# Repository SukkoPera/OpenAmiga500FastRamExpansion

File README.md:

# OpenAmiga500FastRamExpansion
OpenAmiga500FastRamExpansion is an Open Hardware 4/8 MB Fast RAM Expansion for the Commodore Amiga 500 Computer.

### Summary
Most low-end Amiga models only came with *Chip RAM*. "Big Box" models allowed for a different type of memory to be installed, known as *Fast RAM*, where *fast* means that it's dedicated to the main processor, so that it doesn't have to compete with the other chips in order to gain access to it (as is the case with Chip RAM). While both Chip and Fast RAM are limited in size, you can have at least a few MB of the latter on all Amigas (usually up to 8), while the former can never exceed 2 MB.

OpenAmiga500FastRamExpansion will allow you to add 4 or 8 MB of Fast RAM to your Amiga 500. This way you will be able to run more applications at once and more quickly. If you combine it with [a chip RAM expansion](http://eab.abime.net/showthread.php?t=85395), you will also be able to run almost all games supported by WHDLoad, pushing your Amiga to its limits.

OpenAmiga500FastRamExpansion is basically a clone of [a RAM expansion produced by Kipper2K a few years ago](http://eab.abime.net/showthread.php?t=64218), based on [an earlier design by lvd/NedoPC](http://lvd.nedopc.com/Projects/a600_8mb/index.html). He has since stopped producing and selling these cards and I thought it was a pity that he didn't open his designs and actually took all of them down, as this card is quite cheap to build and really useful. So I set about recreating it from scratch.

### Memory Compatibility
The required RAM Type is 16 Mbit (1M×16) DRAM in the SOJ-42 package with up to 70-80 ns access time. It is 5v-only DRAM (not SD(!)RAM) often found in old 72-pin SIMMs, EDO chips might work or not. All chips having *8160* in their part number should be OK.

|Model          |Maker             |Tested             |Working            |Data Sheet                                                                                                                                                                 |Notes                                                                                |
|---------------|------------------|:-----------------:|:-----------------:|:-------------------------------------------------------------------------------------------------------------------------------------------------------------------------:|-------------------------------------------------------------------------------------|
|AS4C1M116E5    |Alliance          |||                                                                                                                                                                           |Tested by @Homer799                                                                  |
|GM71C18160     |Hynix/LGS         |||                                                                    |Tested by lvd in his original project                                                |
|HY5118164B     |Hynix             |||                                                                                                                                                                           |Tested by @Sgw32                                                                     |
|KM416C1200AJ   |SEC               |||                                                                                                                                                                           |Reported working by Ronald Baer                                                      |
|KM416C1204AJ/BJ|SEC               |||                                             |Reported working by screwbreaker                                                     |
|MSM5118160     |OKI               |||                                                                    |Tested by lvd in his original project                                                |
|TMS41860DZ     |Texas Instruments |||                                                                                                                                                                           |Reported working by Ronald Baer                                                      |
|TMS41869DZ     |Texas Instruments |  |                   |                                                                                                                                                                           |                                                                                     |
|4218160        |NEC               |||                                                                                                                                                                           |Reported working by Ronald Baer                                                      |
|4218165        |NEC               |||                          |Tested by SukkoPera                                                                  |
|VG2618165BJ    |Vanguard          |||                                                                                                                                                                           |Tested by @Csordi                                                                    |
|NN5118160AJ-60 |NPN               |||                                                                                                                                                                           |Tested by @RipZ                                                                      |

RAM chips can either be soldered directly to the board or installed in sockets. While soldering the chips might not be trivial for the unexperienced, sockets for the SOJ-42 package are hard to find and not really easier to solder either, so the choice is up to you.

### Assembly and Installation
Normally it is not necessary to mount all the decoupling capacitors. I usually skip C4, C5, C9, C12, C15 and C18. Maybe C1 can be left out as well if you have a good power supply, your choice. R4 must be chosen according to the particular led you will be using for LD1. Actually you are free to skip LD1 and R4 altogether, if you hate power LEDs.

After everything has been soldered, you will need to program the CPLD. Whenever you do so, **make sure to carefully remove the board from your Amiga, or you might risk damaging it**. You can find the firmware [here](firmware/V2), along with instructions on how to flash it. You can provide power through the pads of C1 if you need to do so.

Make sure to use the [correct firmware version](#Firmware), according to how many chips you soldered on the board! For the 4 MB version, solder U7 and U8 only and use the dedicated firmware.

When assembly is complete, open your A500 and remove the top shield. Carefully remove the CPU (largest chip at bottom left of the board), using a chip extractor or a small flat screwdriver, taking care not to break/bend any pins. Plug it on the board, matching the orientation, and plug the whole board in the CPU socket.

Before reassembling your case, I recommend to run [SysTest/Amiga Test Kit](https://github.com/keirf/Amiga-Stuff). Use the Memory option (<kbd>F1</kbd>), it must show 4/8 MB of Fast RAM. Then start the Memory Test (<kbd>F1</kbd> again) and let it run for 50-100 rounds: if it doesn't find any errors, you are probably good to go. If you get any errors, check your solder joints, starting from actual the RAM chips, as the SOJ package is not very hand-soldering-friendly.

### Firmware
If you are using Kickstart 2.x or higher you should use the latest V2 firmware [here](firmware/V2) noting that it requires an ATF1504AS rather than the older version's ATF1502

If you are using Kickstart 1.3 you will need to use the [V1 Firmware here](firmware/V1)

#### V2 Firmware new features
Thanks to two new features this board is compatible with other autoconfig devices and should no longer cause any conflicts
* Autoconfig snooping - This board will configure itself after every other Autoconfig device
* Autosizing - The firmware will shrink the configured size automatically to make it fit within the remaining free memory pool (8M/4M/2M/1M).

#### V1 Firmware Limitations
The V1 Firmware for OpenAmiga500FastRamExpansion only has a partial implementation of the AutoConfig protocol. This has the following consequences:
- On the A500 it will only work if nothing is connected to the side expansion port (or if whatever is connected does NOT use AutoConfig).
- On the A2000 it will only work if nothing is installed in the Zorro expansion slots (again: or if whatever you installed there does not use AutoConfig).
- On the CDTV it just won't work (since the DMAC uses AutoConfig and is built-in.)

Because of these limitations it is recommended to use the new Firmware where possible, this will allow your board to coexist with other Autoconfig devices.
If you cannot use the V2 firmware for some reason (i.e you use Kickstart 1.3) then the only way to get around these limitations is flashing an alternative firmware on the board which does not use AutoConfig, but then you will have to add the RAM manually in Workbench, using the `addmem` utility. More on this soon.

### License
The OpenAmiga500FastRamExpansion documentation, including the design itself, is copyright &copy; SukkoPera 2019.

OpenAmiga500FastRamExpansion is Open Hardware licensed under the [CERN OHL v. 1.2](http://ohwr.org/cernohl).

You may redistribute and modify this documentation under the terms of the CERN OHL v.1.2. This documentation is distributed *as is* and WITHOUT ANY EXPRESS OR IMPLIED WARRANTIES whatsoever with respect to its functionality, operability or use, including, without limitation, any implied warranties OF MERCHANTABILITY, SATISFACTORY QUALITY, FITNESS FOR A PARTICULAR PURPOSE or infringement. We expressly disclaim any liability whatsoever for any direct, indirect, consequential, incidental or special damages, including, without limitation, lost revenues, lost profits, losses resulting from business interruption or loss of data, regardless of the form of action or legal theory under which the liability may be asserted, even if advised of the possibility or likelihood of such damages.

A copy of the full license is included in file [LICENSE.pdf](LICENSE.pdf), please refer to it for applicable conditions. In order to properly deal with its terms, please see file [LICENSE_HOWTO.pdf](LICENSE_HOWTO.pdf).

The contact points for information about manufactured Products (see section 4.2) are listed in file [PRODUCT.md](PRODUCT.md).

Any modifications made by Licensees (see section 3.4.b) shall be recorded in file [CHANGES.md](CHANGES.md).

The Documentation Location of the original project is https://github.com/SukkoPera/OpenAmiga500FastRamExpansion/.

### Support the Project
Since the project is open you are free to get the PCBs made by your preferred manufacturer, however in case you want to support the development, you can order them from PCBWay through this link:

You get my gratitude and cheap, professionally-made and good quality PCBs, I get some credit that will help with this and [other projects](https://www.pcbway.com/project/member/shareproject/?bmbid=41100). You won't even have to worry about the various PCB options, it's all pre-configured for you!

Also, if you still have to register to that site, [you can use this link](https://www.pcbway.com/setinvite.aspx?inviteid=41100) to get some bonus initial credit (and yield me some more).

Again, if you want to use another manufacturer, feel free to, don't feel obligated :). But then you can buy me a coffee if you want:

### Get Help
If you need help or have questions, you can join [the official Telegram group](https://t.me/joinchat/HUHdWBC9J9JnYIrvTYfZmg).

### Thanks
- lvd for the initial design and the support he gave me during development
- Kipper2K for making his boards
- majinga for helping with the testing

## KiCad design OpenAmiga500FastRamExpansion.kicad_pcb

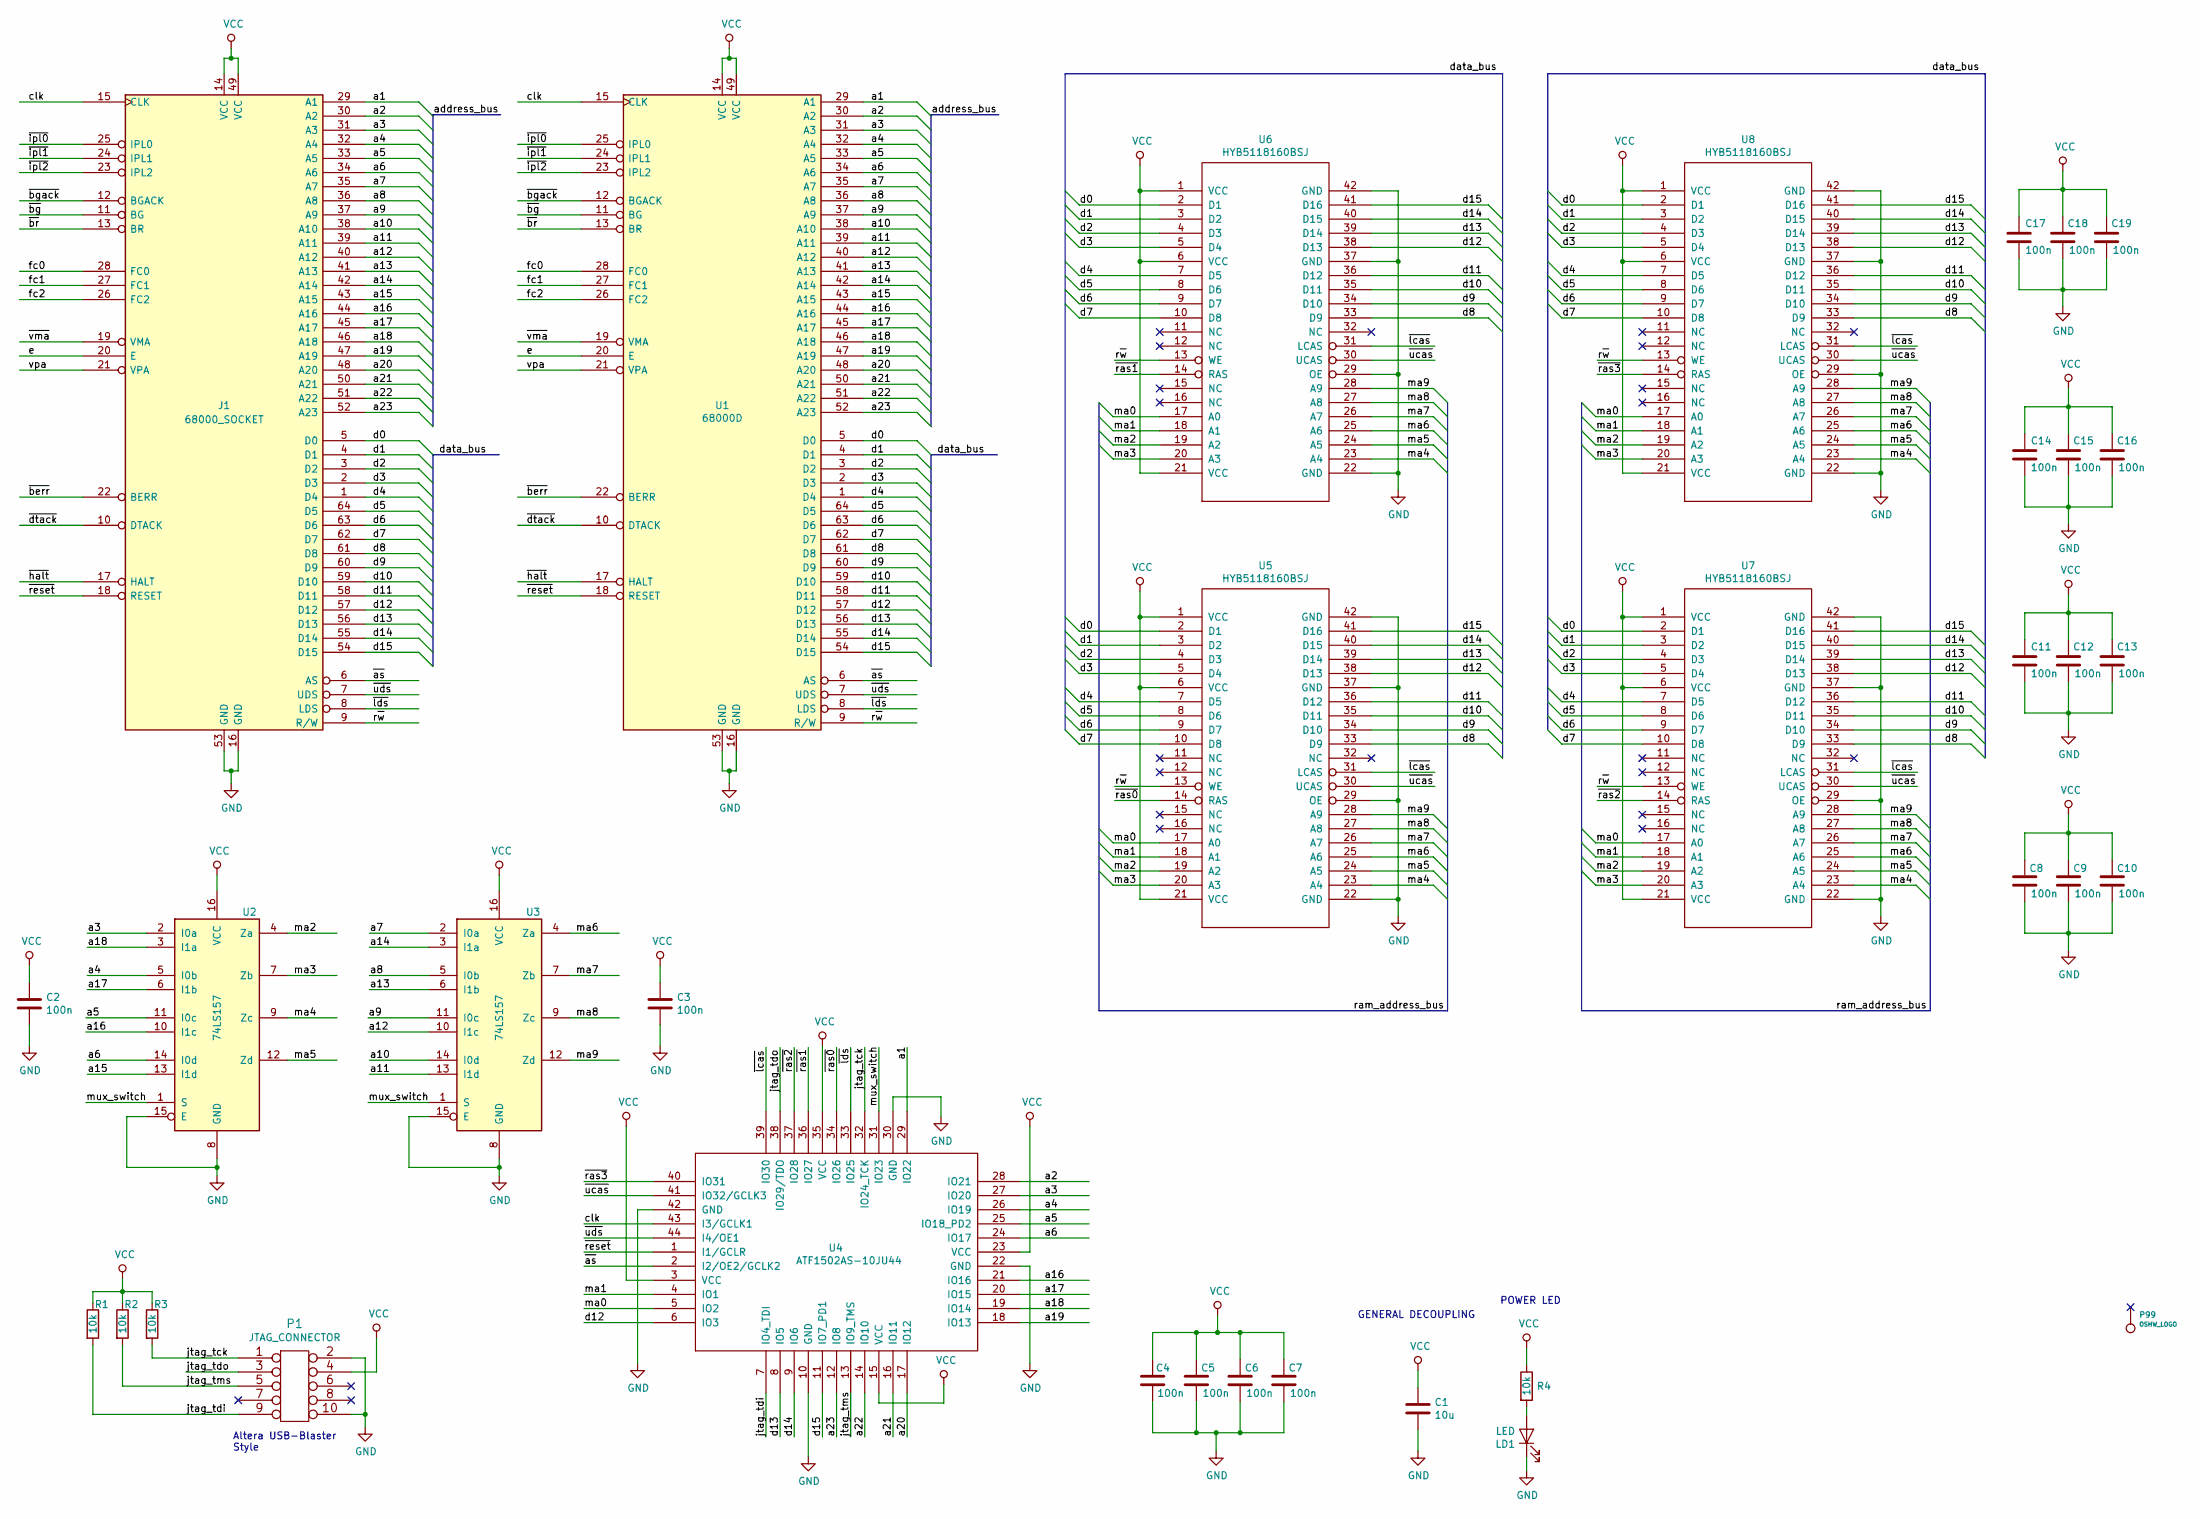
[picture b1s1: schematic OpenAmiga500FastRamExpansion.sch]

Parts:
C1: 10u; CP_Radial_D5.0mm_P2.00mm
C2, C3, C4, C5, C6, C7, C8, C9, C10, C11, C12, C13, C14, C15, C16, C17, C18, C19: 100n; C_0805_2012Metric_Pad1.15x1.40mm_HandSolder
J1: 68000_SOCKET; DIP-64_W22.86mm_Socket_LongPads_Socket
LD1: LED; LED_0805_HandSoldering_ModSilkS
P1: JTAG_CONNECTOR; IDC-Header_2x05_P2.54mm_Vertical
P99: OSHW_LOGO; OSHW-Logo2_7.3x6mm_Copper
R1, R2, R3, R4: 10k; R_0805_2012Metric_Pad1.15x1.40mm_HandSolder
U1: 68000D; DIP-64_W22.86mm_Socket_LongPads_IC
U2, U3: 74LS157; SOIC-16_3.9x9.9mm_P1.27mm
U4: ATF1502AS-10JU44; PLCC-44_THT-Socket
U5, U6, U7, U8: HYB5118160BSJ; SOJ-42-LongPads

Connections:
/a1: J1.29 (A1), U1.29 (A1), U4.29 (IO22)
/a2: J1.30 (A2), U1.30 (A2), U4.28 (IO21)
/a3: J1.31 (A3), U1.31 (A3), U2.2 (I0a), U4.27 (IO20)
/a4: J1.32 (A4), U1.32 (A4), U2.5 (I0b), U4.26 (IO19)
/a5: J1.33 (A5), U1.33 (A5), U2.11 (I0c), U4.25 (IO18_PD2)
/a6: J1.34 (A6), U1.34 (A6), U2.14 (I0d), U4.24 (IO17)
/a7: J1.35 (A7), U1.35 (A7), U3.2 (I0a)
/a8: J1.36 (A8), U1.36 (A8), U3.5 (I0b)
/a9: J1.37 (A9), U1.37 (A9), U3.11 (I0c)
/a10: J1.38 (A10), U1.38 (A10), U3.14 (I0d)
/a11: J1.39 (A11), U1.39 (A11), U3.13 (I1d)
/a12: J1.40 (A12), U1.40 (A12), U3.10 (I1c)
/a13: J1.41 (A13), U1.41 (A13), U3.6 (I1b)
/a14: J1.42 (A14), U1.42 (A14), U3.3 (I1a)
/a15: J1.43 (A15), U1.43 (A15), U2.13 (I1d)
/a16: J1.44 (A16), U1.44 (A16), U2.10 (I1c), U4.21 (IO16)
/a17: J1.45 (A17), U1.45 (A17), U2.6 (I1b), U4.20 (IO15)
/a18: J1.46 (A18), U1.46 (A18), U2.3 (I1a), U4.19 (IO14)
/a19: J1.47 (A19), U1.47 (A19), U4.18 (IO13)
/a20: J1.48 (A20), U1.48 (A20), U4.17 (IO12)
/a21: J1.50 (A21), U1.50 (A21), U4.16 (IO11)
/a22: J1.51 (A22), U1.51 (A22), U4.14 (IO10)
/a23: J1.52 (A23), U1.52 (A23), U4.12 (IO8)
/clk: J1.15 (CLK), U1.15 (CLK), U4.43 (I3/GCLK1)
/d0: J1.5 (D0), U1.5 (D0), U5.2 (D1), U6.2 (D1), U7.2 (D1), U8.2 (D1)
/d1: J1.4 (D1), U1.4 (D1), U5.3 (D2), U6.3 (D2), U7.3 (D2), U8.3 (D2)
/d2: J1.3 (D2), U1.3 (D2), U5.4 (D3), U6.4 (D3), U7.4 (D3), U8.4 (D3)
/d3: J1.2 (D3), U1.2 (D3), U5.5 (D4), U6.5 (D4), U7.5 (D4), U8.5 (D4)
/d4: J1.1 (D4), U1.1 (D4), U5.7 (D5), U6.7 (D5), U7.7 (D5), U8.7 (D5)
/d5: J1.64 (D5), U1.64 (D5), U5.8 (D6), U6.8 (D6), U7.8 (D6), U8.8 (D6)
/d6: J1.63 (D6), U1.63 (D6), U5.9 (D7), U6.9 (D7), U7.9 (D7), U8.9 (D7)
/d7: J1.62 (D7), U1.62 (D7), U5.10 (D8), U6.10 (D8), U7.10 (D8), U8.10 (D8)
/d8: J1.61 (D8), U1.61 (D8), U5.33 (D9), U6.33 (D9), U7.33 (D9), U8.33 (D9)
/d9: J1.60 (D9), U1.60 (D9), U5.34 (D10), U6.34 (D10), U7.34 (D10), U8.34 (D10)
/d10: J1.59 (D10), U1.59 (D10), U5.35 (D11), U6.35 (D11), U7.35 (D11), U8.35 (D11)
/d11: J1.58 (D11), U1.58 (D11), U5.36 (D12), U6.36 (D12), U7.36 (D12), U8.36 (D12)
/d12: J1.57 (D12), U1.57 (D12), U4.6 (IO3), U5.38 (D13), U6.38 (D13), U7.38 (D13), U8.38 (D13)
/d13: J1.56 (D13), U1.56 (D13), U4.8 (IO5), U5.39 (D14), U6.39 (D14), U7.39 (D14), U8.39 (D14)
/d14: J1.55 (D14), U1.55 (D14), U4.9 (IO6), U5.40 (D15), U6.40 (D15), U7.40 (D15), U8.40 (D15)
/d15: J1.54 (D15), U1.54 (D15), U4.11 (IO7_PD1), U5.41 (D16), U6.41 (D16), U7.41 (D16), U8.41 (D16)
/e: J1.20 (E), U1.20 (E)
/fc0: J1.28 (FC0), U1.28 (FC0)
/fc1: J1.27 (FC1), U1.27 (FC1)
/fc2: J1.26 (FC2), U1.26 (FC2)
/jtag_tck: P1.1, R3.2, U4.32 (IO24_TCK)
/jtag_tdi: P1.9, R1.2, U4.7 (IO4_TDI)
/jtag_tdo: P1.3, U4.38 (IO29/TDO)
/jtag_tms: P1.5, R2.2, U4.13 (IO9_TMS)
/ma0: U4.5 (IO2), U5.17 (A0), U6.17 (A0), U7.17 (A0), U8.17 (A0)
/ma1: U4.4 (IO1), U5.18 (A1), U6.18 (A1), U7.18 (A1), U8.18 (A1)
/ma2: U2.4 (Za), U5.19 (A2), U6.19 (A2), U7.19 (A2), U8.19 (A2)
/ma3: U2.7 (Zb), U5.20 (A3), U6.20 (A3), U7.20 (A3), U8.20 (A3)
/ma4: U2.9 (Zc), U5.23 (A4), U6.23 (A4), U7.23 (A4), U8.23 (A4)
/ma5: U2.12 (Zd), U5.24 (A5), U6.24 (A5), U7.24 (A5), U8.24 (A5)
/ma6: U3.4 (Za), U5.25 (A6), U6.25 (A6), U7.25 (A6), U8.25 (A6)
/ma7: U3.7 (Zb), U5.26 (A7), U6.26 (A7), U7.26 (A7), U8.26 (A7)
/ma8: U3.9 (Zc), U5.27 (A8), U6.27 (A8), U7.27 (A8), U8.27 (A8)
/ma9: U3.12 (Zd), U5.28 (A9), U6.28 (A9), U7.28 (A9), U8.28 (A9)
/mux_switch: U2.1 (S), U3.1 (S), U4.31 (IO23)
/r~w: J1.9 (R/W), U1.9 (R/W), U5.13 (WE), U6.13 (WE), U7.13 (WE), U8.13 (WE)
/vpa: J1.21 (VPA), U1.21 (VPA)
/~as: J1.6 (AS), U1.6 (AS), U4.2 (I2/OE2/GCLK2)
/~berr: J1.22 (BERR), U1.22 (BERR)
/~bg: J1.11 (BG), U1.11 (BG)
/~bgack: J1.12 (BGACK), U1.12 (BGACK)
/~br: J1.13 (BR), U1.13 (BR)
/~dtack: J1.10 (DTACK), U1.10 (DTACK)
/~halt: J1.17 (HALT), U1.17 (HALT)
/~ipl0: J1.25 (IPL0), U1.25 (IPL0)
/~ipl1: J1.24 (IPL1), U1.24 (IPL1)
/~ipl2: J1.23 (IPL2), U1.23 (IPL2)
/~lcas: U4.39 (IO30), U5.31 (LCAS), U6.31 (LCAS), U7.31 (LCAS), U8.31 (LCAS)
/~lds: J1.8 (LDS), U1.8 (LDS), U4.33 (IO25)
/~ras0: U4.34 (IO26), U5.14 (RAS)
/~ras1: U4.36 (IO27), U6.14 (RAS)
/~ras2: U4.37 (IO28), U7.14 (RAS)
/~ras3: U4.40 (IO31), U8.14 (RAS)
/~reset: J1.18 (RESET), U1.18 (RESET), U4.1 (I1/GCLR)
/~ucas: U4.41 (IO32/GCLK3), U5.30 (UCAS), U6.30 (UCAS), U7.30 (UCAS), U8.30 (UCAS)
/~uds: J1.7 (UDS), U1.7 (UDS), U4.44 (I4/OE1)
/~vma: J1.19 (VMA), U1.19 (VMA)
GND: C1.2, C2.2, C3.2, C4.2, C5.2, C6.2, C7.2, C8.2, C9.2, C10.2, C11.2, C12.2, C13.2, C14.2, C15.2, C16.2, C17.2, C18.2, C19.2, J1.16 (GND), J1.53 (GND), LD1.1 (K), P1.2, P1.10, U1.16 (GND), U1.53 (GND), U2.8 (GND), U2.15 (E), U3.8 (GND), U3.15 (E), U4.10 (GND), U4.22 (GND), U4.30 (GND), U4.42 (GND), U5.22 (GND), U5.29 (OE), U5.37 (GND), U5.42 (GND), U6.22 (GND), U6.29 (OE), U6.37 (GND), U6.42 (GND), U7.22 (GND), U7.29 (OE), U7.37 (GND), U7.42 (GND), U8.22 (GND), U8.29 (OE), U8.37 (GND), U8.42 (GND)
unnamed: LD1.2 (A), R4.2
VCC: C1.1, C2.1, C3.1, C4.1, C5.1, C6.1, C7.1, C8.1, C9.1, C10.1, C11.1, C12.1, C13.1, C14.1, C15.1, C16.1, C17.1, C18.1, C19.1, J1.14 (VCC), J1.49 (VCC), P1.4, R1.1, R2.1, R3.1, R4.1, U1.14 (VCC), U1.49 (VCC), U2.16 (VCC), U3.16 (VCC), U4.3 (VCC), U4.15 (VCC), U4.23 (VCC), U4.35 (VCC), U5.1 (VCC), U5.6 (VCC), U5.21 (VCC), U6.1 (VCC), U6.6 (VCC), U6.21 (VCC), U7.1 (VCC), U7.6 (VCC), U7.21 (VCC), U8.1 (VCC), U8.6 (VCC), U8.21 (VCC)

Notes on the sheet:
Altera USB-Blaster Style
GENERAL DECOUPLING
POWER LED

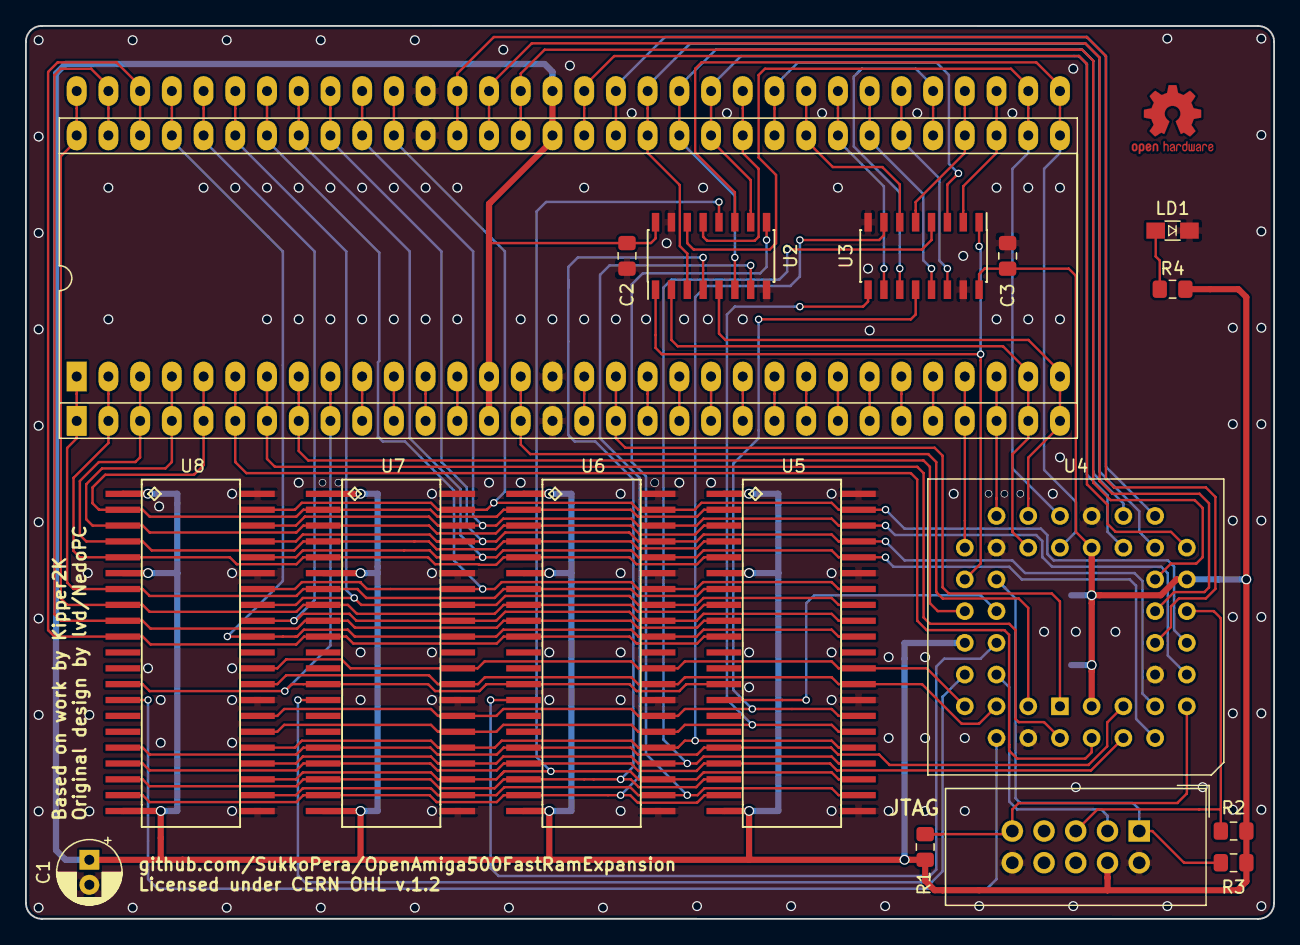
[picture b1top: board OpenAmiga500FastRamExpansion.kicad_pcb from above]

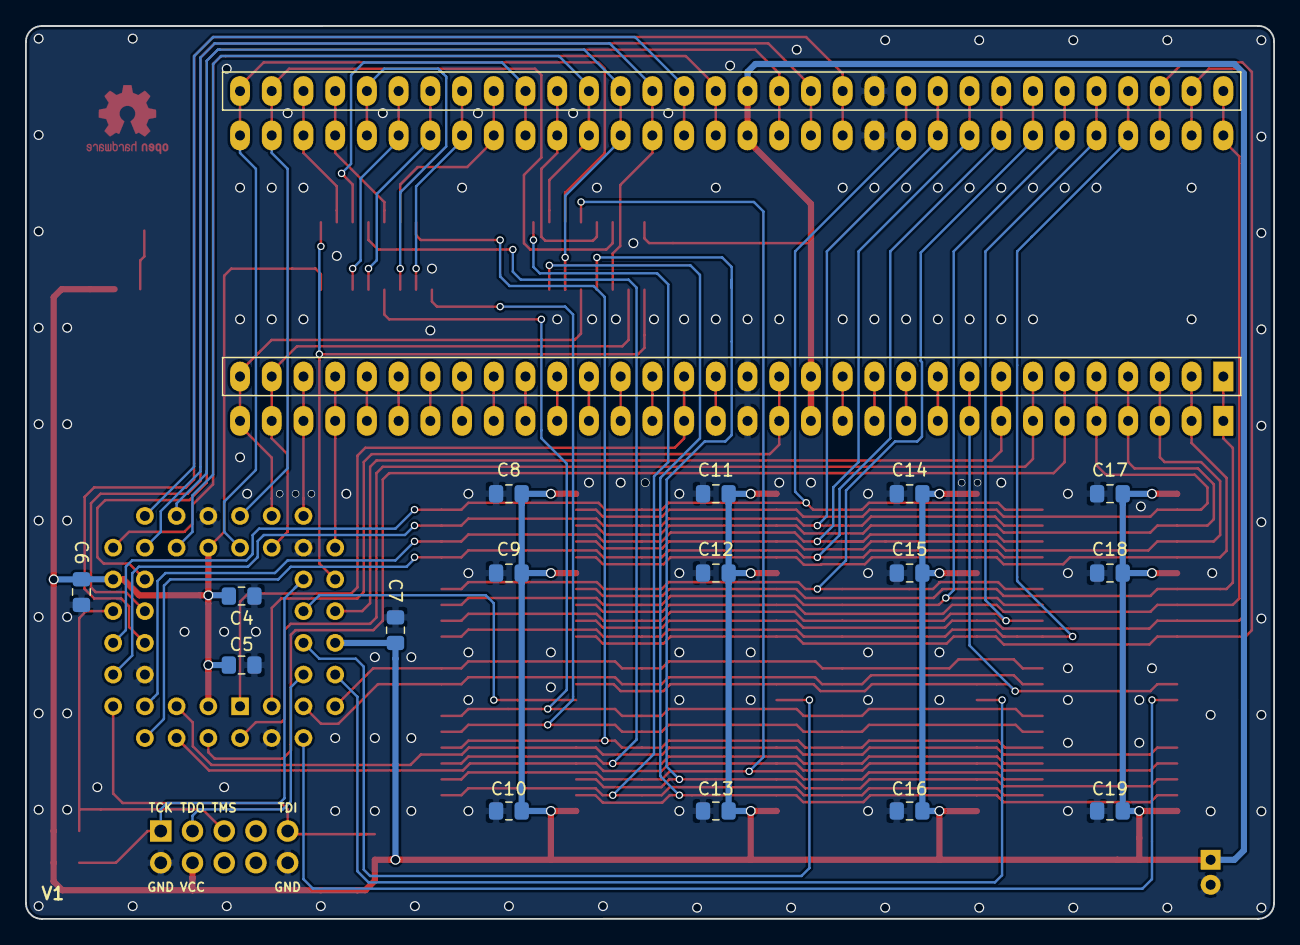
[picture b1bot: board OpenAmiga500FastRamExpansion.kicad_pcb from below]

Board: 2 copper layers, 100.0 x 71.5 mm, 35 parts (16 on the bottom side), 84 nets.

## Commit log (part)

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2019-02-28 Add .gitignore
2019-02-28 Initial commit, schematic should be OK, PCB routing started
2019-03-01 Completed routing of data bus from CPU to RAM
2019-03-02 Almost there...
2019-03-02 Routing complete Ground stitching and some refinements TBD
2019-03-02 Refinements here and there
2019-03-02 Stitched perimeter and more refinements
2019-03-03 More and more and more and more and more refinements...
2019-03-03 Add JTAG connector pinout
2019-03-03 Ready for prototypes
2019-03-03 Add missing footprint
2019-03-03 Add renders
2019-03-03 Just can't get enough of vias
2019-03-03 Remove old pin names
2019-05-19 Add CPLD firmware
2019-05-19 Fix #1 and we're ready for V1
2019-05-19 Add Yes/No images
2019-05-19 Revert "Add Yes/No images"
    This reverts commit b87a44d5065ce376d625c41538a7d2bb2d8aebaa.
2019-05-19 Add doc image
2019-05-21 Fix link to A500 Chip RAM Expansion
2019-07-22 Update compatibility list
2019-07-22 Add contributor names to compatibility list
2019-08-19 Fix typo
2019-08-19 Add notes about -10JU44 CPLD
2019-08-22 Fix BSDL stuff
2019-08-24 Add KM416C1204BJ to compatibility list
2019-08-24 KM416C1204BJ is actually a newer version of KM416C1204AJ
2019-09-04 Improve Quartus instructions
2019-12-27 Improve README
2019-12-27 Add Windows flashing package
2019-12-27 Minor corrections
2020-12-25 doc: add CPLD erase instructions
2021-01-22 Add 8MB non-AutoConfig firmware and other useful stuff
2021-05-08 Add note on parallel port programmer Thanks to Patrick Kerkhof!
2021-06-13 Add GottaGoFast Autosnoop firmware
2021-06-15 Fixup AutoSnoop for KS 3.1.4/3x0/3.2
2021-10-19 Fix #5
    Thanks @Homer799, @Sgw32, @Csordi, @RipZ

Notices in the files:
OpenAmiga500FastRamExpansion.kicad_pcb:
Licensed under CERN OHL v.1.2
